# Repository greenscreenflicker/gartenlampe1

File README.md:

# Gartenlampe1
Simple LED Board acception 11V-30V and producing lots of lumens.
Integrates Buck Converter. Simple and secured with fuse.

LED: Luxeon3020
Buck: AL8805

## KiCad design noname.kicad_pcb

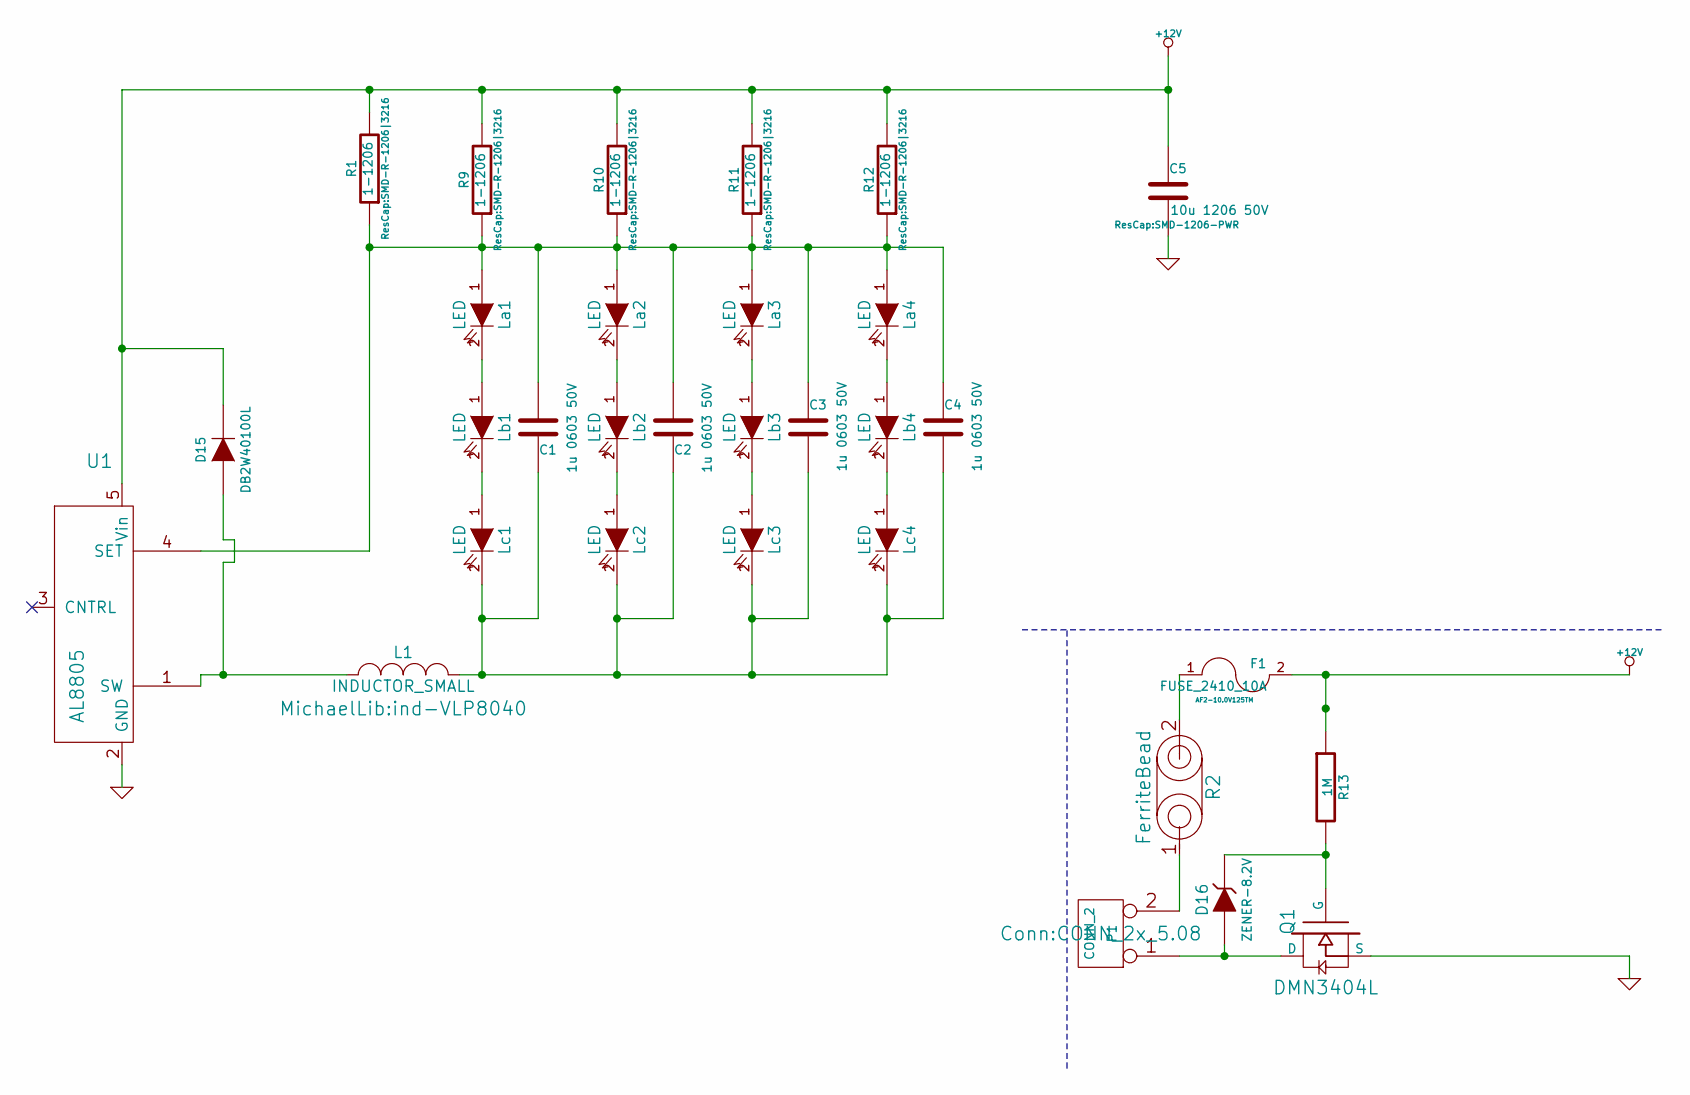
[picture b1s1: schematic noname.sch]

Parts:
C1, C2, C3, C4: 1u 0603 50V; SMD-C-0603|1608
C5: 10u 1206 50V; SMD-1206-PWR
D15: DB2W40100L; SOD323-W
D16: ZENER-8.2V
F1: FUSE_2410_10A; SMD-R-2010|3225; Part AF2-10.0V125TM
L1: INDUCTOR_SMALL; ind-VLP8040
La1, La2, La3, La4: LED; LUXEON3020
Lb1, Lb2, Lb3, Lb4: LED; LUXEON3020
Lc1, Lc2, Lc3, Lc4: LED; LUXEON3020
P1: CONN_2; CONN_2x_5.08
Q1: DMN3404L; SOT23
R1, R9, R10, R11, R12: 1-1206; SMD-R-1206|3216
R2: FerriteBead; SMD-1206-PWR
R13: 1M; SMD-R-0603|1608
U1: AL8805; SOT23-5

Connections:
+12V: C5.1, D15.2 (K), F1.2, R1.2, R9.2, R10.2, R11.2, R12.2, R13.1, U1.5 (Vin)
GND: C5.2, Q1.2 (S), U1.2 (GND)
unnamed: C1.1, C2.1, C3.2, C4.2, L1.2, Lc1.2 (K), Lc2.2 (K), Lc3.2 (K), Lc4.2 (K)
unnamed: C1.2, C2.2, C3.1, C4.1, La1.1 (A), La2.1 (A), La3.1 (A), La4.1 (A), R1.1, R9.1, R10.1, R11.1, R12.1, U1.4 (SET)
unnamed: D15.1 (A), L1.1, U1.1 (SW)
unnamed: D16.1 (A), P1.1, Q1.3 (D)
unnamed: D16.2 (K), Q1.1 (G), R13.2
unnamed: F1.1, R2.2
unnamed: La1.2 (K), Lb1.1 (A)
unnamed: La2.2 (K), Lb2.1 (A)
unnamed: La3.2 (K), Lb3.1 (A)
unnamed: La4.2 (K), Lb4.1 (A)
unnamed: Lb1.2 (K), Lc1.1 (A)
unnamed: Lb2.2 (K), Lc2.1 (A)
unnamed: Lb3.2 (K), Lc3.1 (A)
unnamed: Lb4.2 (K), Lc4.1 (A)
unnamed: P1.2 (PM), R2.1

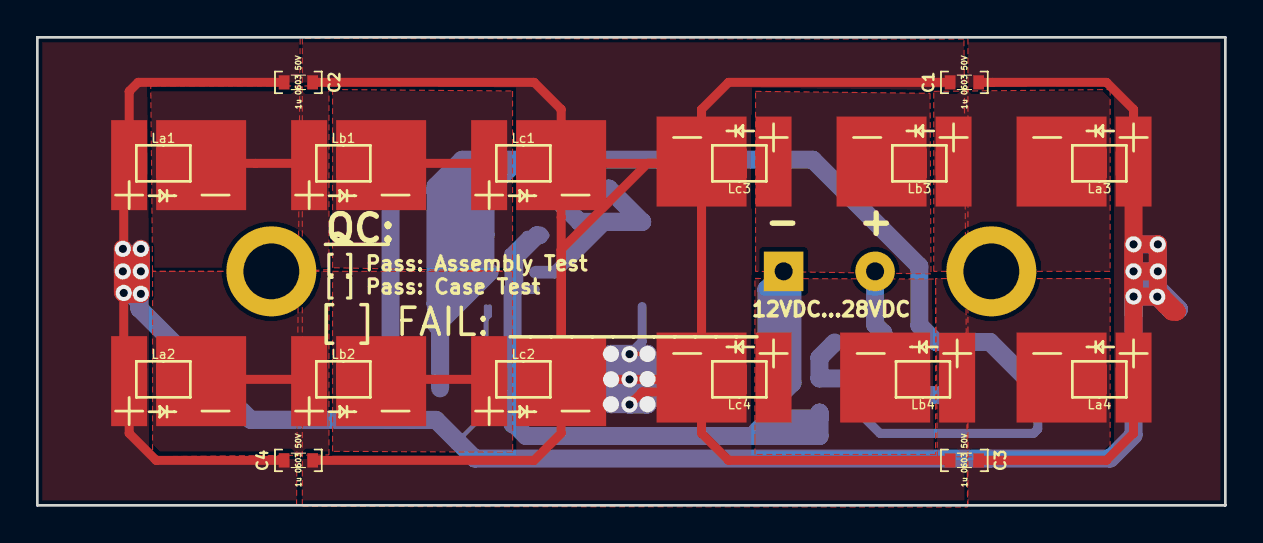
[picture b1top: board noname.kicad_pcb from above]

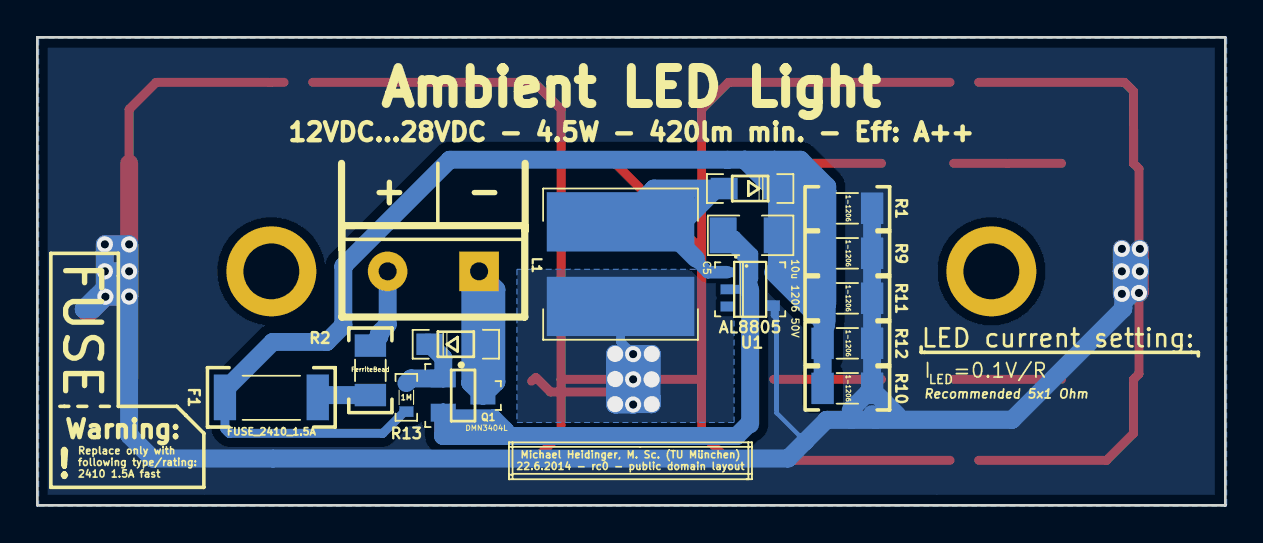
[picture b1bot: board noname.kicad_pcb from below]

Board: 2 copper layers, 66.0 x 26.0 mm, 33 parts (15 on the bottom side), 17 nets.

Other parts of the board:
P5, P5#2: CONN_1; 1PIN_MECHANICAL

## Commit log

2016-09-04 added PCB
2016-09-04 Usability update
    +Readme
    +Folder structure

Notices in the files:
noname.kicad_pcb:
22.6.2014 - rc0 - public domain layout
